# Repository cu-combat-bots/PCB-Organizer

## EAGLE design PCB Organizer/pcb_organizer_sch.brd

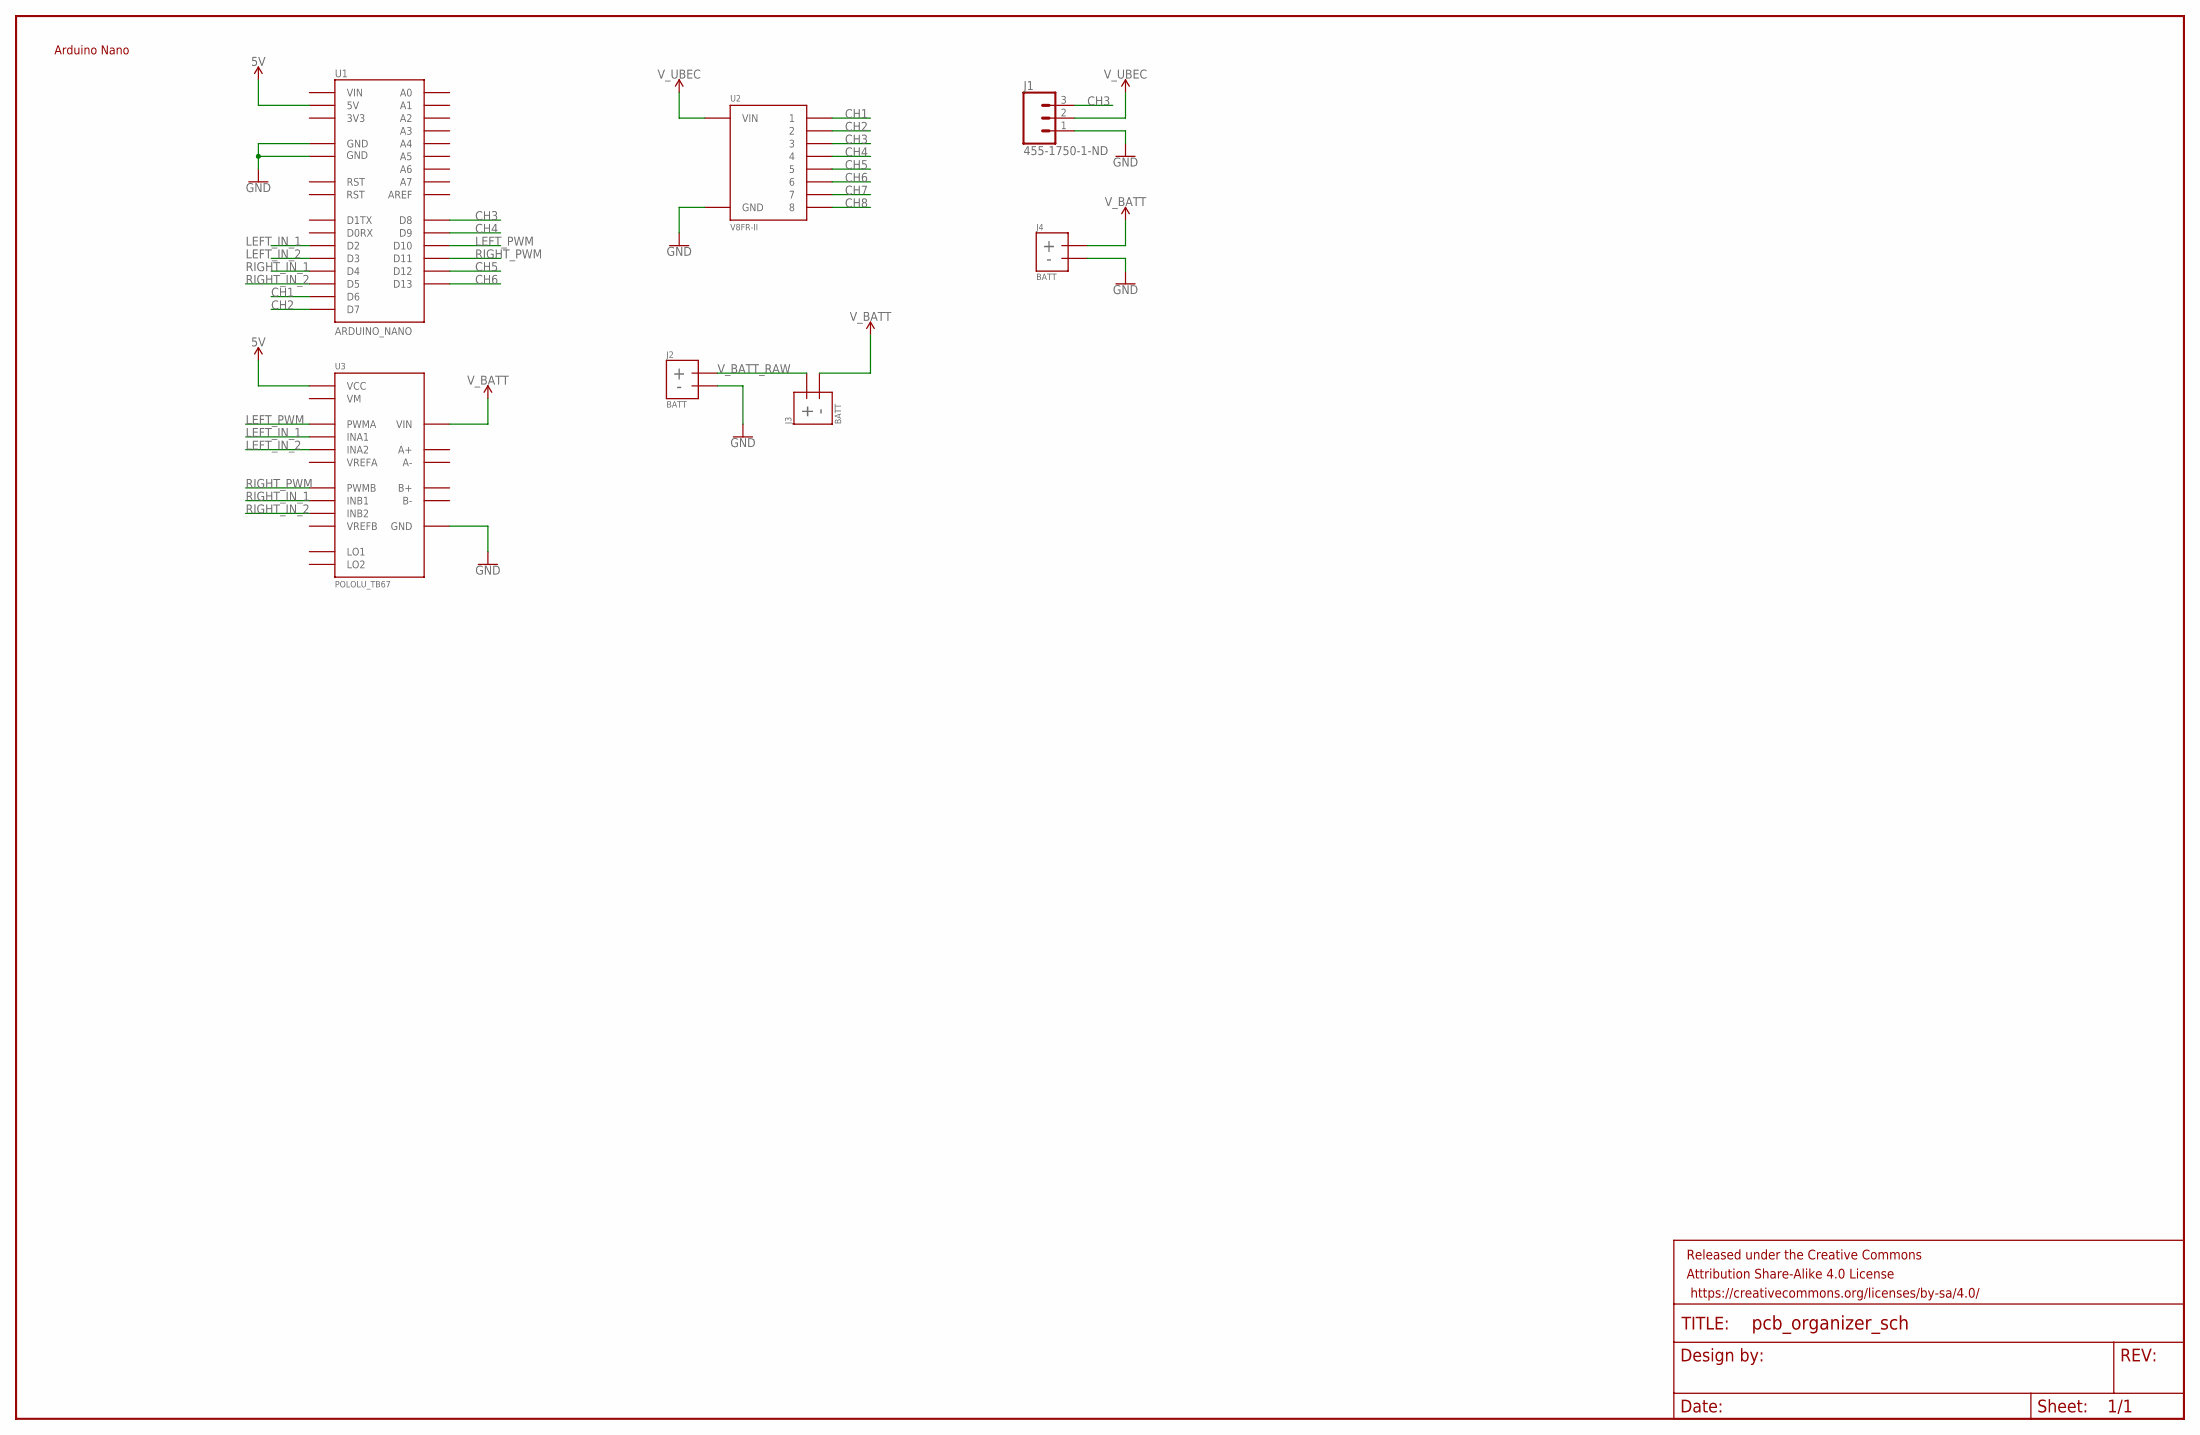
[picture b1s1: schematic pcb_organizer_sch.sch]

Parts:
FRAME1: FRAME-LEDGER; CREATIVE_COMMONS
J1: 455-1750-1-ND; 1X03
J2, J3, J4: BATT; CONN_2_10AUG
U1: ARDUINO_NANO
U2: V8FR-II
U3: POLOLU_TB67

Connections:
5V: U1.5V, U3.VCC
CH1: U1.D6, U2.1
CH2: U1.D7, U2.2
CH3: J1.3, U1.D8, U2.3
CH4: U1.D9, U2.4
CH5: U1.D12, U2.5
CH6: U1.D13, U2.6
CH7: U2.7
CH8: U2.8
GND: J1.1, J2.-, J4.-, U1.GND, U1.GND_@16 (GND), U2.GND_1 (GND), U2.GND_2 (GND), U2.GND_3 (GND), U2.GND_4 (GND), U2.GND_5 (GND), U2.GND_6 (GND), U2.GND_7 (GND), U2.GND_8 (GND), U3.GND, U3.GND@14 (GND), U3.GND@15 (GND)
LEFT_IN_1: U1.D2, U3.INA1
LEFT_IN_2: U1.D3, U3.INA2
LEFT_PWM: U1.D10, U3.PWMA
RIGHT_IN_1: U1.D4, U3.INB1
RIGHT_IN_2: U1.D5, U3.INB2
RIGHT_PWM: U1.D11, U3.PWMB
V_BATT: J3.-, J4.+, U3.VIN
V_BATT_RAW: J2.+, J3.+
V_UBEC: J1.2, U2.VIN_1 (VIN), U2.VIN_2 (VIN), U2.VIN_3 (VIN), U2.VIN_4 (VIN), U2.VIN_5 (VIN), U2.VIN_6 (VIN), U2.VIN_7 (VIN), U2.VIN_8 (VIN)

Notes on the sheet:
Arduino Nano

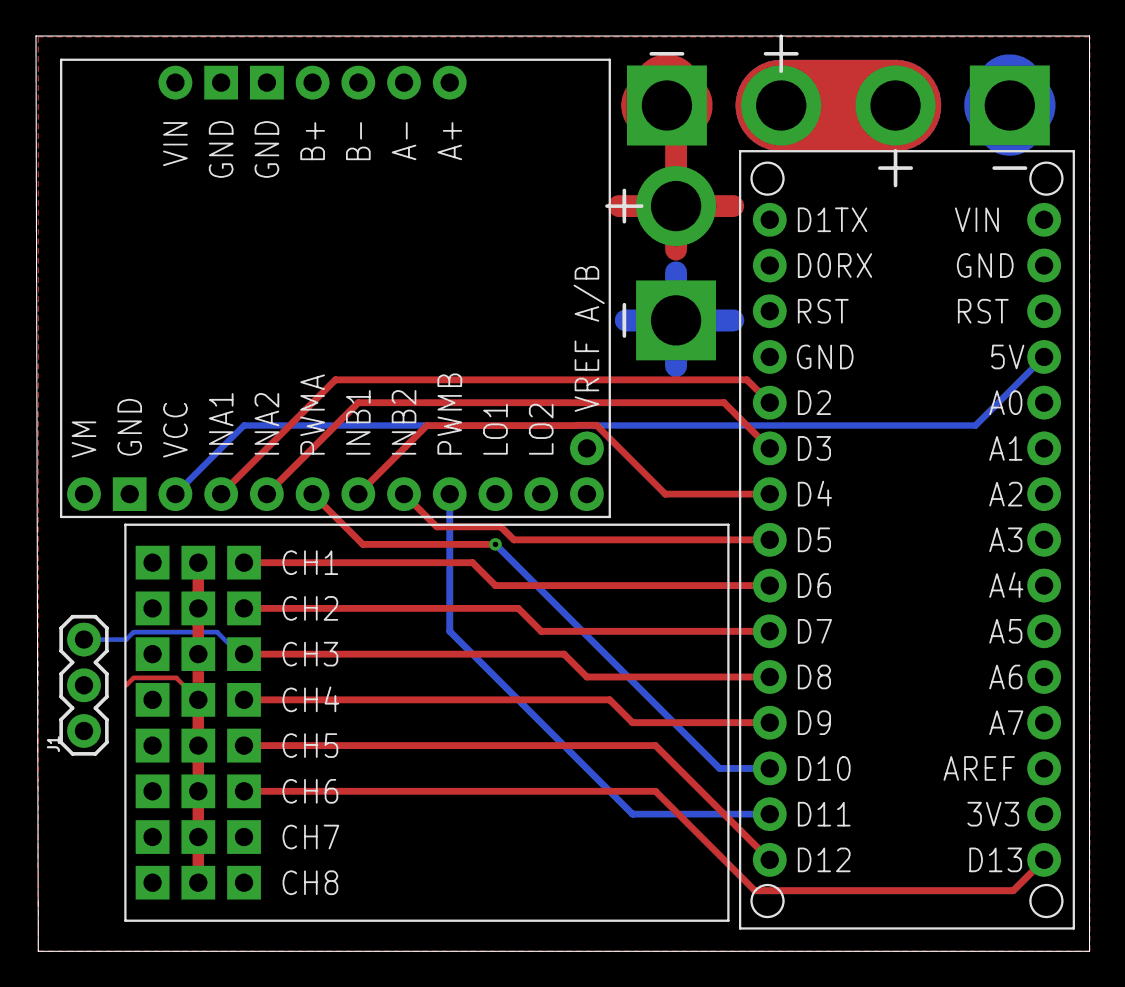
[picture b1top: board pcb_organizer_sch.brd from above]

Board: 2 copper layers, 58.5 x 50.9 mm, 8 parts (0 on the bottom side), 17 nets.

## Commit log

2019-06-14 Initial Commit; Created Arduino Nano device
2019-06-15 Added footprint for V8FR-II receiver
2019-06-20 Added Pololu TB67 motor driver to the library, board, and schematic
2019-06-21 Finished Schematic and laid out the board. No routing
2019-06-21 Finished routing
2019-06-23 Increased polygon connection trace thickness
2019-07-04 Fixes #5, #4
2019-07-04 Fixed #1

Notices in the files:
parts and their libraries:
SparkFun-Aesthetics: Licensing: Creative Commons ShareAlike 4.0 International - https://creativecommons.org/licenses/by-sa/4.0
SparkFun-Aesthetics: Released under the Creative Commons
SparkFun-Aesthetics: https://creativecommons.org/licenses/by-sa/4.0
